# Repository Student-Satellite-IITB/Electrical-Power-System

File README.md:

# ELECTRICAL POWER SYSTEM

This repository contains all software and hardware for the 
Electrical Power subsystem for the IITBSSP CubeSat mission

Current status: 
- EPS PDB and PMB Assembly
- Battery Unit Development Board
- Power Distribution and Regulation Development Board
- MATLAB/Simulink model of EPS in development
- Testing of Solar Input Development Board
- Testing of Control Unit Development Board

Completed:
- EPS PDB Board Design
- EPS PMB Board Design
- Solar Input Development Board
- EPS Control Unit Development Board

Maintained by:
- Ameya Marakarkandy <ameya.marakarkandy@gmail.com>
- Yash Paritkar <paritkary25@gmail.com>

[SSP Website](https://www.aero.iitb.ac.in/satlab/) | 
[Satellite 101 Wiki](https://www.aero.iitb.ac.in/satelliteWiki/index.php/Satellite_101)

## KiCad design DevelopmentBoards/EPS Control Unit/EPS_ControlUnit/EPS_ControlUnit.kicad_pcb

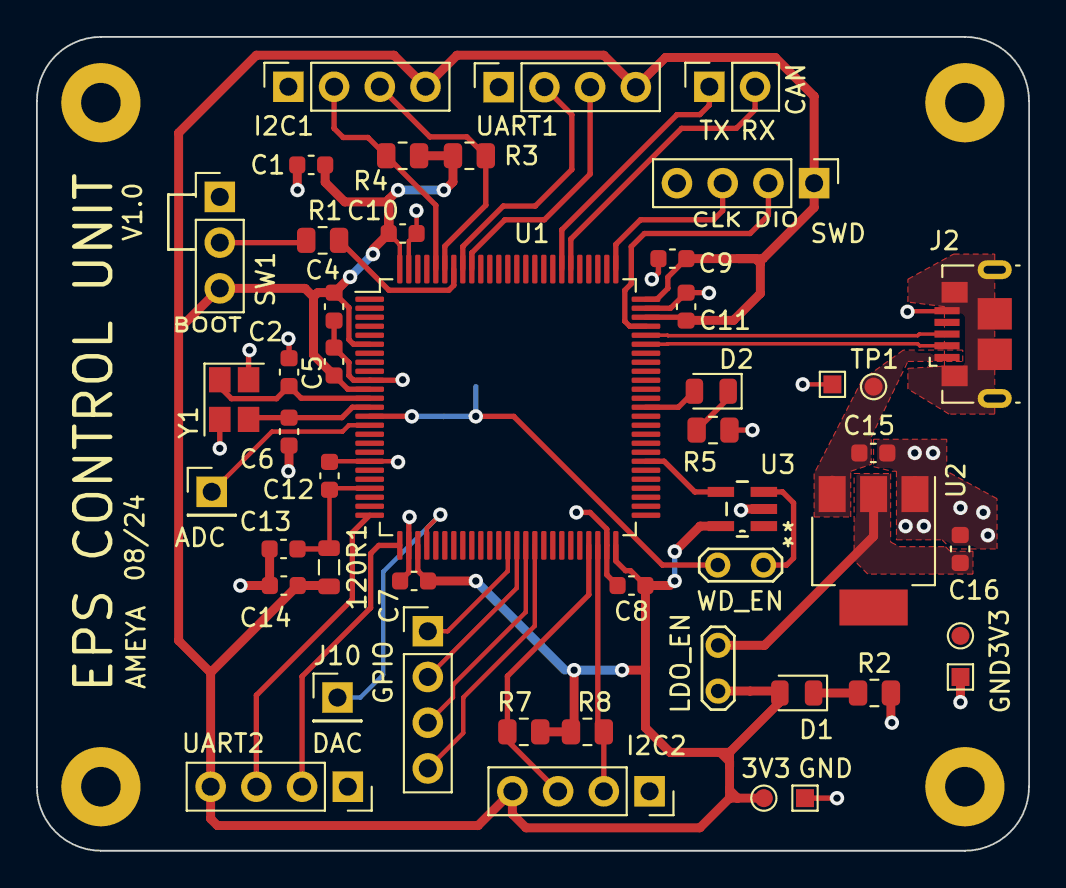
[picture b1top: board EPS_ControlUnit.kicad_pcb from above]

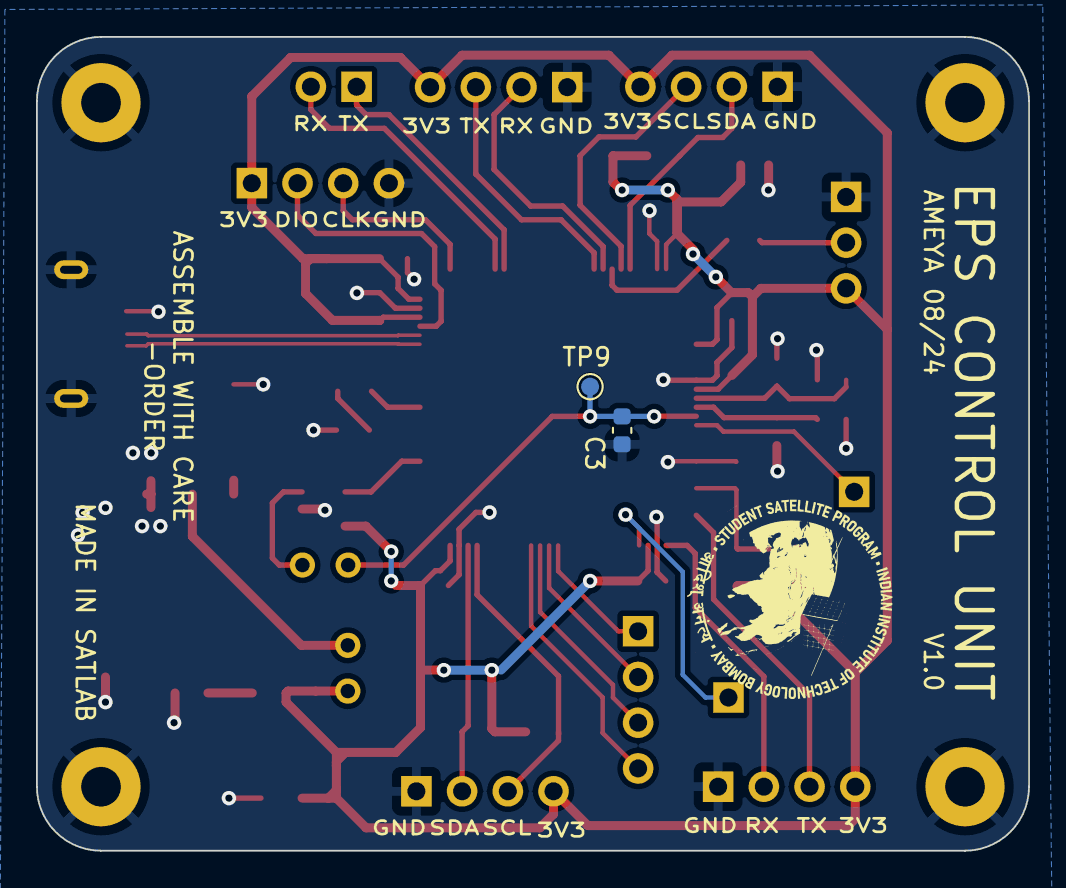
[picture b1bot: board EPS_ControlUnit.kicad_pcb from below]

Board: 2 copper layers, 55.1 x 45.2 mm, 54 parts (2 on the bottom side), 35 nets.

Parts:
3V3, 3V3#2: TestPoint; TestPoint_Pad_D1.0mm
120R1: FerriteBead; L_0805_2012Metric
C1: 10uF; C_0603_1608Metric
C2, C6: 10pF; C_0603_1608Metric
C3, C4, C5, C7, C8, C9, C10, C11: 100nF; C_0603_1608Metric
C12: 10nF; C_0603_1608Metric
C13, C14: 1uF; C_0603_1608Metric
C15, C16: 22uF; C_0603_1608Metric
D1: POWER_LED; LED_0805_2012Metric
D2: EPS_LED; LED_0805_2012Metric
GND: TestPoint; TestPoint_Pad_1.0x1.0mm
GND#2: TestPoint; TestPoint_Pad_1.0x1.0mm
H1, H2, H3, H4: MountingHole_Pad; MountingHole_2.2mm_M2_Pad
J1, J8: Conn_01x04_Pin; PinHeader_1x04_P2.54mm_Vertical
J2: USB_B_Micro; USB_Micro-B_GCT_USB3076-30-A
J3, J4, J5, J6: Conn_01x04_Pin; PinSocket_1x04_P2.54mm_Vertical
J7: Conn_01x02_Pin; PinSocket_1x02_P2.54mm_Vertical
J9, J10: Conn_01x01_Pin; PinHeader_1x01_P2.54mm_Vertical
LDO_EN: Jumper_2_Bridged; TestPoint_2Pads_Pitch2.54mm_Drill0.8mm
R1: 10k; R_0805_2012Metric
R2, R3, R4, R5, R7, R8: 1k5; R_0805_2012Metric
SW1: SW_SPDT; PinHeader_1x03_P2.54mm_Vertical
TP1, TP9: TestPoint; TestPoint_Pad_D1.0mm
TP2: TestPoint; TestPoint_Pad_1.0x1.0mm
U1: STM32L476VET6; LQFP-100_14x14mm_P0.5mm
U2: AMS1117-3.3; SOT-223-3_TabPin2
U3: TPS3824-33QDBVRQ1; tps3824
WD_EN: Jumper_2_Bridged; TestPoint_2Pads_Pitch2.54mm_Drill0.8mm
Y1: 32MHz; Crystal_SMD_Abracon_ABM8AIG-4Pin_3.2x2.5mm

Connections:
3V3_EPS: 3V3.1, 120R1.2, C1.1, C4.1, C5.1, C7.1, C8.1, C9.1, C10.1, C11.1, C14.1, D1.2 (A), J1.1, J3.4, J4.4, J5.4, J6.4, LDO_EN.2 (B), R3.1, R4.1, R7.1, R8.1, SW1.3 (C), U1.6 (VBAT), U1.11 (VDD), U1.28 (VDD), U1.50 (VDD), U1.73 (VDDUSB), U1.75 (VDD), U1.100 (VDD), U3.5 (VDD)
+3.3VA: 120R1.1, C12.1, C13.1, U1.22 (VDDA)
/3V3_LDO: 3V3#2.1, C16.1, LDO_EN.1 (A), U2.2 (VO)
/ADC: J9.1, U1.15 (PC0)
/BOOT0: R1.2, U1.94 (BOOT0)
/CAN_RX: J7.2, U1.81 (PD0)
/CAN_TX: J7.1, U1.82 (PD1)
/DAC: J10.1, U1.29 (PA4)
/EPS_LED: D2.2 (A), U1.63 (PC6)
/GPIO1: J8.1, U1.38 (PE7)
/GPIO2: J8.2, U1.39 (PE8)
/GPIO3: J8.3, U1.40 (PE9)
/GPIO4: J8.4, U1.41 (PE10)
/HSE_IN: C2.1, U1.12 (PH0), Y1.1
/HSE_OUT: C6.1, U1.13 (PH1), Y1.3
/I2C1_SCL: J3.3, R3.2, U1.95 (PB8)
/I2C1_SDA: J3.2, R4.2, U1.96 (PB9)
/I2C2_SCL: J5.3, R7.2, U1.47 (PB10)
/I2C2_SDA: J5.2, R8.2, U1.48 (PB11)
/LED_CATHODE: D1.1 (K), R2.1
/NRST: C3.1, TP9.1, U1.14 (NRST), WD_EN.2 (B)
/SWCLK: J1.3, U1.76 (PA14)
/SWDIO: J1.2, U1.72 (PA13)
/SW_BOOT0: R1.1, SW1.2 (B)
/UART1_RX: J4.2, U1.93 (PB7)
/UART1_TX: J4.3, U1.92 (PB6)
/UART2_RX: J6.2, U1.26 (PA3)
/UART2_TX: J6.3, U1.25 (PA2)
/USB_D+: J2.3 (D+), U1.71 (PA12)
/USB_D-: J2.2 (D-), U1.70 (PA11)
/WDI: U1.57 (PD10), U3.4 (WDI)
/WDI_RESET: U3.3 (RESET), WD_EN.1 (A)
GND: C1.2, C2.2, C3.2, C4.2, C5.2, C6.2, C7.2, C8.2, C9.2, C10.2, C11.2, C12.2, C13.2, C14.2, C15.2, C16.2, GND.1, GND#2.1, H1.1, H2.1, H3.1, H4.1, J1.4, J2.5 (GND), J2.6 (Shield), J3.1, J4.1, J5.1, J6.1, R2.2, R5.2, SW1.1 (A), TP2.1, U1.10 (VSS), U1.19 (VSSA), U1.27 (VSS), U1.49 (VSS), U1.74 (VSS), U1.99 (VSS), U2.1 (GND), U3.2 (GND), Y1.2, Y1.4
unnamed: D2.1 (K), R5.1
VBUS: C15.1, J2.1 (VBUS), TP1.1, U2.3 (VI)

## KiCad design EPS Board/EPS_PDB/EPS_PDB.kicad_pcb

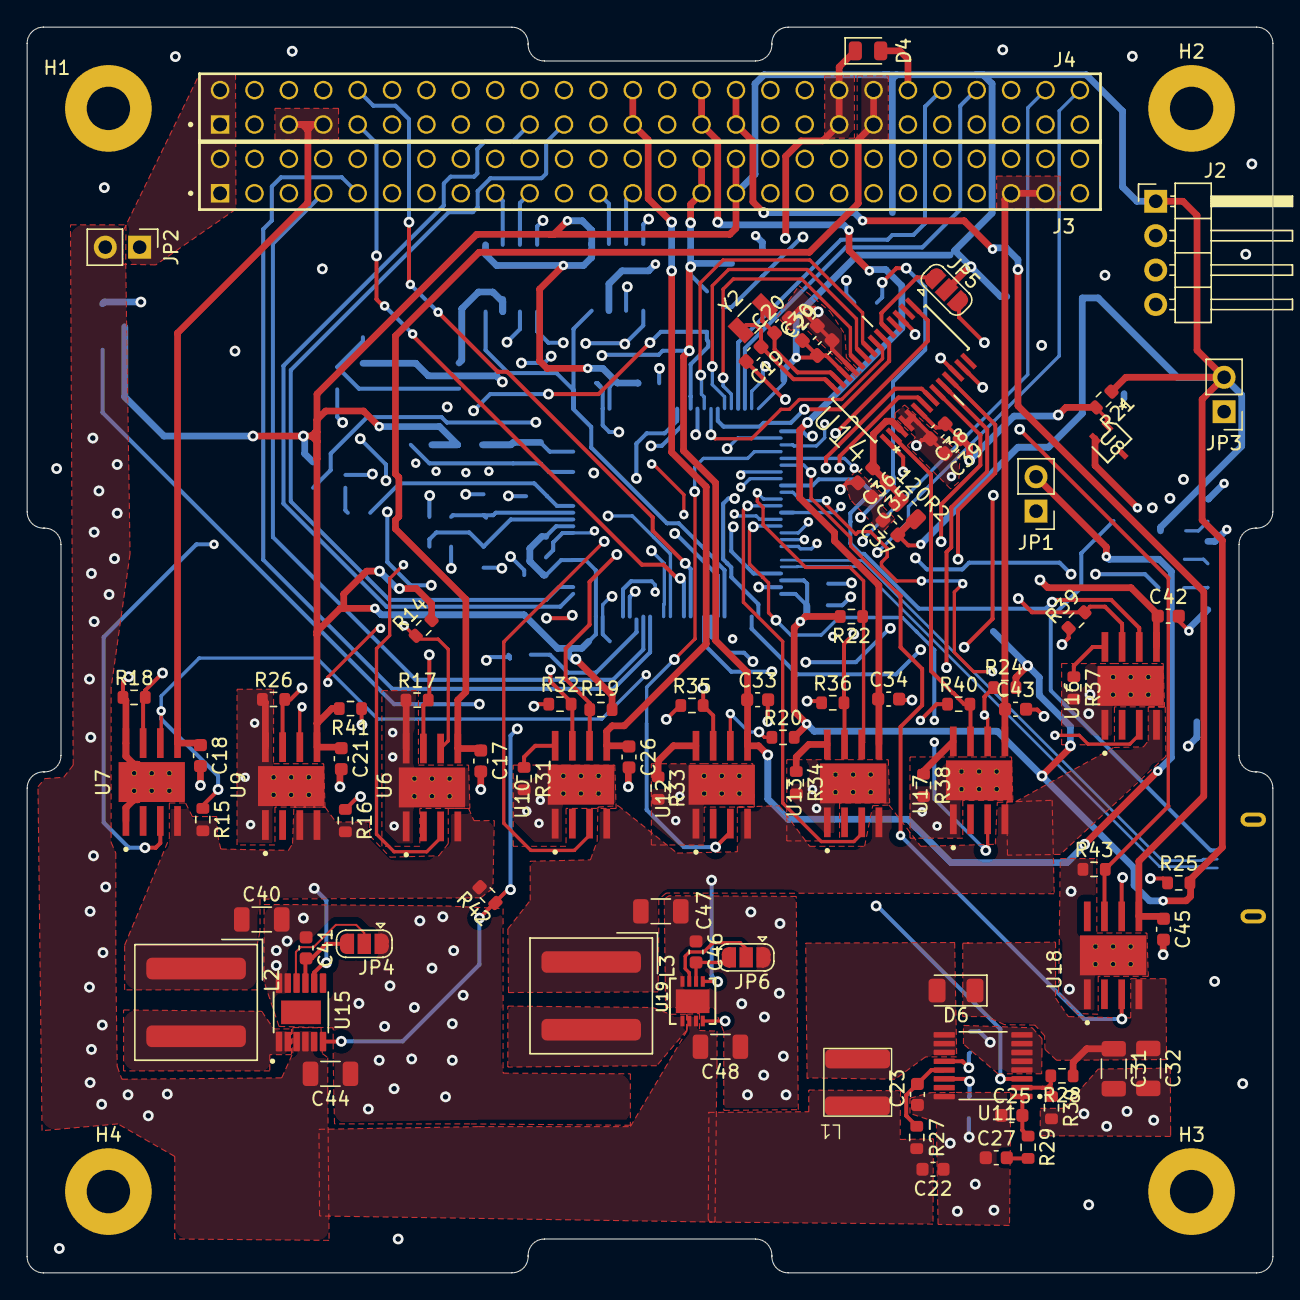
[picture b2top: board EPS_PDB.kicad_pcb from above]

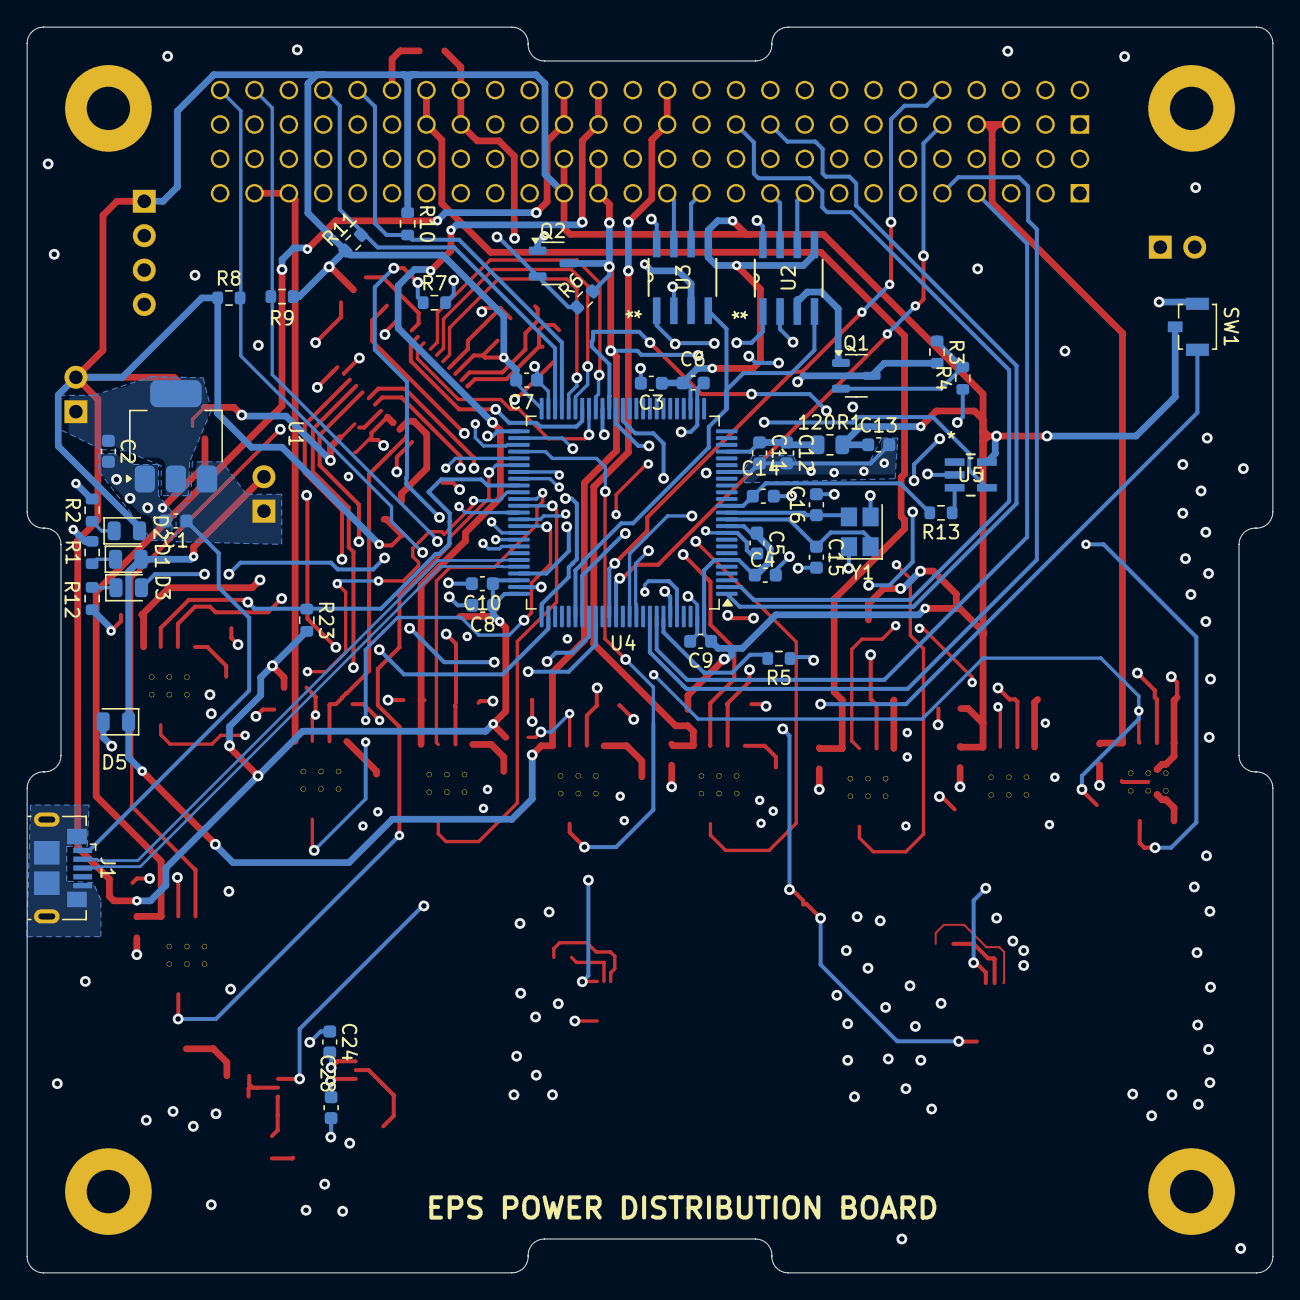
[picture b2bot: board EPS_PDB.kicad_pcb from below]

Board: 4 copper layers, 92.0 x 92.0 mm, 140 parts (47 on the bottom side), 113 nets.

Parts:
120R1, 120R2: FerriteBead; R_0805_2012Metric
C1, C2: 22uF; C_0603_1608Metric
C3, C29, C38: 10uF; C_0603_1608Metric
C4, C5, C6, C7, C8, C9, C10, C14: 100nF; C_0603_1608Metric
C11, C28, C35: 10nF; C_0603_1608Metric
C12, C13, C17, C18, C21, C26, C33, C34, C36, C37, C42, C43, C45: 1uF; C_0603_1608Metric
C15, C16, C19, C20: 10pF; C_0603_1608Metric
C22: 4.7uF; C_0603_1608Metric
C23: 0.47uF; C_0603_1608Metric
C24: 0.1uF; C_0603_1608Metric
C25: 100pF; C_0603_1608Metric
C27: 3300pF; C_0603_1608Metric
C30, C39: C; C_0603_1608Metric
C31, C32: 4.7uF; C_1206_3216Metric
C40, C47: 47uF; C_1206_3216Metric
C41, C46: 2.2uF; C_0603_1608Metric
C44, C48: 10uF; C_1206_3216Metric
D1: EPS_5V_LED; LED_0805_2012Metric
D2: EPS_3V3_LED; LED_0805_2012Metric
D3: EPS_LED; LED_0805_2012Metric
D4, D5: D_Schottky; D_0805_2012Metric
D6: D; D_1206_3216Metric
H1, H2, H3, H4: MountingHole_Pad; MountingHole_3.2mm_M3_Pad
J1: USB_B_Micro; USB_Micro-B_GCT_USB3076-30-A
J2: Conn_01x04_Pin; PinHeader_1x04_P2.54mm_Horizontal
J3, J4: Conn_02x26_Odd_Even; SAMTEC_ESQ-126-39-G-D
JP1, JP3: USB_POW_EN; PinHeader_1x02_P2.54mm_Vertical
JP2: Jumper_2_Bridged; PinHeader_1x02_P2.54mm_Vertical
JP4, JP6: SolderJumper-3_P1.3mm_Open_RoundedPad1.0x1.5mm
JP5: Jumper_3_Bridged12; SolderJumper-3_P1.3mm_Open_RoundedPad1.0x1.5mm
L1: 8.2uH; WE-XHMI-5050
L2, L3: 2.2uH; L_Wuerth_WE-XHMI-8080
Q1, Q2: PMOS; SOT-23-3
R1, R2, R8, R9, R10, R11, R12: 1k5; R_0603_1608Metric
R3, R6: 100k; R_0603_1608Metric
R4, R7: 100; R_0603_1608Metric
R5, R14, R15, R16, R18, R19, R20, R22, R23, R24, R25, R41, R42: 10k; R_0603_1608Metric
R13: 0; R_0603_1608Metric
R17, R26: 2.2k; R_0603_1608Metric
R21, R28: 130k; R_0603_1608Metric
R27: 10; R_0603_1608Metric
R29: 18k; R_0603_1608Metric
R30: 15k; R_0603_1608Metric
R31, R33, R34, R37, R38: 400k; R_0603_1608Metric
R32: 510; R_0603_1608Metric
R35, R39, R43: 560; R_0603_1608Metric
R36, R40: 1.3k; R_0603_1608Metric
SW1: SW_SPDT; SW_SPST_B3U-1100P
U1: AMS1117-3.3; SOT-223-3_TabPin2
U2, U3: SN65HVD256D; D8
U4: STM32L476VET6; LQFP-100_14x14mm_P0.5mm
U5: TPS3824-33QDBVRQ1; tps3824
U6: TPS259621DDAT 3V3_ADCS; IC_TPS259621DDAT
U7: TPS259621DDAT_3V3_ANT; IC_TPS259621DDAT
U8: TS4061BICT-1.25; SOT323-3L_1P35X2P2X0P65_STM
U9: TPS259621DDAT_3V3_EPS; IC_TPS259621DDAT
U10: TPS259621DDAT_5V_PAY; IC_TPS259621DDAT
U11: LM5000-3MTCX; SOP65P640X120-16N
U12: TPS259621DDAT_5V_EPS; IC_TPS259621DDAT
U13: TPS259621DDAT_5V_OBC; IC_TPS259621DDAT
U14: AD7708BRUZ; SOP65P638X110-28N
U15: LTC3624EMSE-3.3PBF; SOP65P490X110-13N
U16: TPS259621DDAT_5V_ADCS; IC_TPS259621DDAT
U17: TPS259621DDAT_5V_COMM; IC_TPS259621DDAT
U18: TPS259621DDAT_12V_ADCS; IC_TPS259621DDAT
U19: LTC3624IDD-25PBF; DFN-8_DD
Y1: 32MHz; Crystal_SMD_Abracon_ABM8AIG-4Pin_3.2x2.5mm
Y2: 32.768kHz; Crystal_SMD_3215-2Pin_3.2x1.5mm

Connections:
3V3_EPS: 120R1.2, 120R2.2, C3.1, C4.1, C5.1, C6.1, C7.1, C8.1, C9.1, C10.1, C13.1, C21.1, C29.1, C30.1, C37.1, D2.2 (A), J2.1, J3.31, J3.32, JP3.2 (B), JP5.2 (C), R8.1, R9.1, R10.1, R11.1, R14.2, R19.2, R20.2, R21.1, R22.2, R23.2, R24.2, R25.2, R41.2, SW1.3 (C), U2.5 (VRXD), U3.5 (VRXD), U4.6 (VBAT), U4.11 (VDD), U4.28 (VDD), U4.50 (VDD), U4.73 (VDDUSB), U4.75 (VDD), U4.100 (VDD), U5.5 (VDD), U9.5 (OUT), U14.26 (DVDD)
5V_EPS: C33.1, D1.2 (A), D5.1 (K), J3.29, J3.30, JP1.2 (B), Q1.3 (S), Q2.3 (S), R3.2, R6.2, U12.5 (OUT)
+3.3VA: 120R1.1, 120R2.1, C11.1, C12.1, C35.1, C36.1, U4.22 (VDDA), U14.3 (AVDD)
/3V3_ADCS: C17.1, J4.39, J4.40, U6.5 (OUT)
/3V3_ANT: C18.1, J4.5, J4.7, U7.5 (OUT)
/3V3_LDO: C2.1, JP3.1 (A), U1.2 (VO)
/5V_ADCS: C42.1, D4.1 (K), J4.37, J4.38, U16.5 (OUT)
/5V_COMM: C43.1, J3.47, J3.49, U17.5 (OUT)
/5V_OBC: C34.1, J4.29, J4.30, U13.5 (OUT)
/5V_PAY: C26.1, J4.25, J4.26, U10.5 (OUT)
/12V_ADCS: C45.1, J4.31, J4.32, U18.5 (OUT)
/ANT_DEPLOY: J4.9, U4.87 (PD6)
/ANT_DEPLOY_STATUS: J4.10, U4.86 (PD5)
/CAN_A_H: J3.19, U2.7 (CANH)
/CAN_A_L: J3.17, U2.6 (CANL)
/CAN_B_H: J3.25, U3.7 (CANH)
/CAN_B_L: J3.23, U3.6 (CANL)
/EN_3V3_ADCS: U4.58 (PD11), U6.3 (EN/UVLO)
/EN_3V3_ANT: U4.67 (PA8), U7.3 (EN/UVLO)
/EN_5V_ADCS: U4.60 (PD13), U16.3 (EN/UVLO)
/EN_5V_COMM: U4.65 (PC8), U17.3 (EN/UVLO)
/EN_5V_EPS: U4.54 (PB15), U12.3 (EN/UVLO)
/EN_5V_OBC: U4.62 (PD15), U13.3 (EN/UVLO)
/EN_5V_PAY: U4.52 (PB13), U10.3 (EN/UVLO)
/EN_12V_ADCS: U4.56 (PD9), U18.3 (EN/UVLO)
/EPS Control Unit/BOOT0: R5.2, U4.94 (BOOT0)
/EPS Control Unit/CAN_RX: U2.4 (RXD), U3.4 (RXD), U4.81 (PD0)
/EPS Control Unit/CAN_SW_A: R4.1, U4.83 (PD2)
/EPS Control Unit/CAN_SW_B: R7.1, U4.84 (PD3)
/EPS Control Unit/CAN_TX: U2.1 (TXD), U3.1 (TXD), U4.82 (PD1)
/EPS Control Unit/EPS_LED: D3.2 (A), U4.63 (PC6)
/EPS Control Unit/HSE_IN: C15.1, U4.12 (PH0), Y1.1
/EPS Control Unit/HSE_OUT: C16.1, U4.13 (PH1), Y1.3
/EPS Control Unit/NRST: C14.1, R13.2, U4.14 (NRST)
/EPS Control Unit/PMOS1_GATE: Q1.2 (G), R3.1, R4.2
/EPS Control Unit/PMOS2_GATE: Q2.2 (G), R6.1, R7.2
/EPS Control Unit/SW_BOOT0: R5.1, SW1.2 (B)
/EPS Control Unit/WDI: U4.38 (PE7), U5.4 (WDI)
/EPS Control Unit/WDI_RESET: R13.1, U5.3 (RESET)
/EPS Power Distribution/1.25VREF: C38.1, C39.1, R21.2, U8.1 (CATHODE), U14.6 (REFIN1(+))
/EPS Power Distribution/3.3V_BUS: C40.1, L2.1, R15.2, R16.2, R42.2, U6.4 (IN), U7.4 (IN), U9.3 (EN/UVLO), U9.4 (IN), U15.8 (FB)
/EPS Power Distribution/5V_BUS: C47.2, L3.1, U10.4 (IN), U12.4 (IN), U13.4 (IN), U16.4 (IN), U17.4 (IN), U19.5 (FB)
/EPS Power Distribution/12V_BUS: C31.1, C32.1, D6.1 (K), R28.1, U18.4 (IN)
/EPS Power Distribution/CLK_IN_ADC: C19.1, U14.28 (XTAL1), Y2.1
/EPS Power Distribution/CLK_OUT_ADC: C20.1, U14.27 (XTAL2), Y2.2
/EPS Power Distribution/FB_12V: R28.2, R30.1, U11.2 (FB)
/EPS Power Distribution/ILM_3V3_ADCS: R17.2, U6.7 (ILM), U14.7 (AIN1)
/EPS Power Distribution/ILM_3V3_ANT: R18.2, U7.7 (ILM), U14.8 (AIN2)
/EPS Power Distribution/ILM_3V3_EPS: R26.2, U9.7 (ILM), U14.9 (AIN3)
/EPS Power Distribution/ILM_5V_ADCS: R39.2, U14.1 (AIN7), U16.7 (ILM)
/EPS Power Distribution/ILM_5V_COMM: R40.2, U14.2 (AIN8), U17.7 (ILM)
/EPS Power Distribution/ILM_5V_EPS: R35.2, U12.7 (ILM), U14.11 (AIN5)
/EPS Power Distribution/ILM_5V_OBC: R36.2, U13.7 (ILM), U14.15 (AIN6)
/EPS Power Distribution/ILM_5V_PAY: R32.2, U10.7 (ILM), U14.10 (AIN4)
/EPS Power Distribution/ILM_12V_ADCS: R43.2, U14.13 (REFIN2(+)/AIN9), U18.7 (ILM)
/EPS Power Distribution/INTVCC_3V3: C41.2, JP4.3 (B), U15.9 (INTVCC)
/EPS Power Distribution/INTVCC_5V: C46.2, JP6.3 (B), U19.6 (INTVCC)
/EPS Power Distribution/MODE_3V3: JP4.2 (C), U15.10 (MODE/SYNC)
/EPS Power Distribution/MODE_5V: JP6.2 (C), U19.7 (MODE/SYNC)
/EPS Power Distribution/SW_3V3: L2.2, U15.1 (SW), U15.2 (SW)
/EPS Power Distribution/SW_5V: L3.2, U19.1 (SW)
/EPS Power Distribution/SW_12V: D6.2 (A), L1.2, U11.9 (SW-1), U11.10 (SW), U11.11 (SW-2)
/EPS Power Distribution/VIN_12V: C23.2, R27.1, U11.13 (VIN)
/FLT_3V3_ADCS: R14.1, U4.57 (PD10), U6.6 (~FLT)
/FLT_3V3_ANT: R15.1, U4.68 (PA9), U7.6 (~FLT)
/FLT_3V3_EPS: R16.1, U4.64 (PC7), U9.6 (~FLT)
/FLT_5V_ADCS: R23.1, U4.59 (PD12), U16.6 (~FLT)
/FLT_5V_COMM: R24.1, U4.66 (PC9), U17.6 (~FLT)
/FLT_5V_EPS: R20.1, U4.53 (PB14), U12.6 (~FLT)
/FLT_5V_OBC: R22.1, U4.61 (PD14), U13.6 (~FLT)
/FLT_5V_PAY: R19.1, U4.51 (PB12), U10.6 (~FLT)
/FLT_12V_ADCS: R25.1, U4.55 (PD8), U18.6 (~FLT)
/HEARTBEAT_ADCS: J4.21, U4.2 (PE3)
/HEARTBEAT_OBC: J4.19, U4.1 (PE2)
/I2C1_SCL: J4.50, R9.2, U4.95 (PB8)
/I2C1_SDA: J4.52, R8.2, U4.96 (PB9)
/I2C2_SCL: J4.44, R10.2, U4.47 (PB10)
/I2C2_SDA: J4.46, R11.2, U4.48 (PB11)
/LED_CATHODE: D2.1 (K), R2.1
/RDY_ADC: U4.42 (PE11), U14.22 (~RDY)
/RESET_ADC: JP5.1 (A), JP5.3 (B), U4.77 (PA15), U14.19 (~RESET)
/SHDN_12V: U4.41 (PE10), U11.3 (SHDN)
/SPI_CS: U4.43 (PE12), U14.21 (~CS)
/SPI_MISO: U4.45 (PE14), U14.23 (DOUT)
/SPI_MOSI: U4.46 (PE15), U14.24 (DIN)
/SPI_SCLK: U4.44 (PE13), U14.20 (SCLK)
/STATUS_3V3: R42.1, U4.40 (PE9), U15.6 (PGOOD)
/STATUS_5V: R41.1, U4.39 (PE8), U19.4 (PGOOD)
/SWCLK: J2.3, U4.76 (PA14)
/SWDIO: J2.2, U4.72 (PA13)
/UART1_CTS: J3.13, U4.90 (PB4)
/UART1_RTS: J3.11, U4.89 (PB3)
/UART1_RX: J3.7, U4.93 (PB7)
/UART1_TX: J3.9, U4.92 (PB6)
/USB_D+: J1.3 (D+), U4.71 (PA12)
/USB_D-: J1.2 (D-), U4.70 (PA11)
/VBUS: C22.2, C44.2, C48.2, JP2.2 (B), L1.1, R27.2, U15.3 (Vin), U15.4 (Vin), U15.5 (RUN), U19.2 (VIN), U19.3 (RUN)
/VBUS0: J3.1, J3.2, J4.1, J4.2, JP2.1 (A)
GND: C1.2, C2.2, C3.2, C4.2, C5.2, C6.2, C7.2, C8.2, C9.2, C10.2, C11.2, C12.2, C13.2, C14.2, C15.2, C16.2, C17.2, C18.2, C19.2, C20.2, C21.2, C22.1, C23.1, C24.1, C25.1, C26.2, C27.1, C28.1, C29.2, C30.2, C31.2, C32.2, C33.2, C34.2, C35.2, C36.2, C37.2, C38.2, C39.2, C40.2, C41.1, C42.2, C43.2, C44.1, C45.2, C46.1, C47.1, C48.1, D4.2 (A), D5.2 (A), H1.1, H2.1, H3.1, H4.1, J1.5 (GND), J1.6 (Shield), J2.4, J3.3, J3.4, J3.15, J3.21, J3.27, J4.3, J4.4, J4.6, J4.8, J4.23, J4.24, J4.27, J4.28, J4.42, J4.48, JP4.1 (A), JP6.1 (A), R1.2, R2.2, R12.2, R17.1, R18.1, R26.1, R30.2, R31.2, R32.1, R33.2, R34.2, R35.1, R36.1, R37.2, R38.2, R39.1, R40.1, R43.1, SW1.1 (A), U1.1 (GND), U2.2 (GND), U2.8 (S), U3.2 (GND), U3.8 (S), U4.10 (VSS), U4.19 (VSSA), U4.27 (VSS), U4.49 (VSS), U4.74 (VSS), U4.99 (VSS), U5.2 (GND), U6.1 (GND), U6.8 (OVCSEL), U6.9 (EXP), U7.1 (GND), U7.8 (OVCSEL), U7.9 (EXP), U8.2 (ANODE), U9.1 (GND), U9.8 (OVCSEL), U9.9 (EXP), U10.1 (GND), U10.9 (EXP), U11.4 (AGND), U11.5 (PGND-1), U11.6 (PGND), U11.7 (PGND-3), U11.8 (PGND-2), U11.16 (TEST), U12.1 (GND), U12.9 (EXP), U13.1 (GND), U13.9 (EXP), U14.4 (AGND), U14.5 (REFIN1(-)), U14.12 (AINCOM), U14.17 (AGND_2), U14.25 (DGND), U15.11 (GND), U15.12 (GND), U16.1 (GND), U16.9 (EXP), U17.1 (GND), U17.9 (EXP), U18.1 (GND), U18.9 (EXP), U19.8 (GND_2), U19.9 (GND), Y1.2, Y1.4
unnamed: C27.2, R29.2
unnamed: D1.1 (K), R1.1
unnamed: D3.1 (K), R12.1
unnamed: Q1.1 (D), U2.3 (VCC)
unnamed: Q2.1 (D), U3.3 (VCC)
unnamed: R31.1, U10.8 (OVCSEL)
unnamed: C24.2, U11.12 (BYP)
unnamed: C25.2, R29.1, U11.1 (COMP)
unnamed: C28.2, U11.14 (SS)
unnamed: R33.1, U12.8 (OVCSEL)
unnamed: R34.1, U13.8 (OVCSEL)
unnamed: R37.1, U16.8 (OVCSEL)
unnamed: R38.1, U17.8 (OVCSEL)
VUSB: C1.1, J1.1 (VBUS), JP1.1 (A), U1.3 (VI)

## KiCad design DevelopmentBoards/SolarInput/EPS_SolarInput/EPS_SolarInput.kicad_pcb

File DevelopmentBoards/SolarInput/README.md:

# EPS Solar Input Unit

Development Board Schematic and PCB Design is complete\
Have sent the PCB for manufacturing\
Yet to order components

Components:
- Molex pico pin connector for input from Solar Panels
- INA232 Current, Volage and Power Measurement with ADC

This document is a work in progress

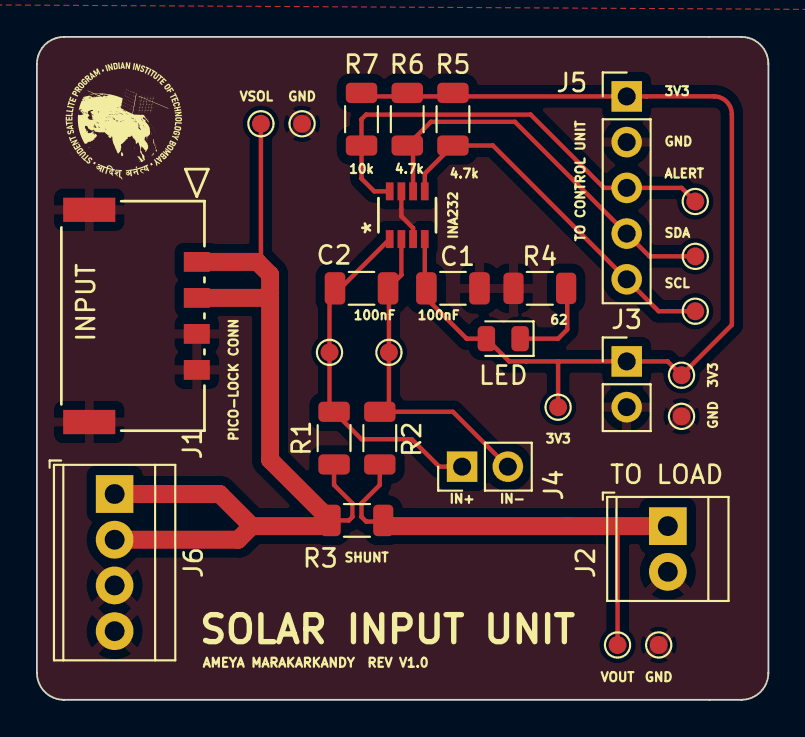
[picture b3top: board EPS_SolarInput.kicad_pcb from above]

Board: 2 copper layers, 40.6 x 36.8 mm, 29 parts (0 on the bottom side), 10 nets.

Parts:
C1: 100nF; C_1206_3216Metric
C2: C2; C_1206_3216Metric
D1: LED; LED_0805_2012Metric
GND: TestPoint; TestPoint_Pad_D1.0mm
INA232: INA232AIDDFR; SOT_32AIDDFR_TEX
J1: 2053380004; CON_2053380004
J2: Screw_Terminal_01x02; TerminalBlock_TE_282834-2_1x02_P2.54mm_Horizontal
J3, J4: Conn_01x02_Socket; PinHeader_1x02_P2.54mm_Vertical
J5: Conn_01x05_Pin; PinHeader_1x05_P2.54mm_Vertical
J6: Screw_Terminal_01x04; TerminalBlock_TE_282834-4_1x04_P2.54mm_Horizontal
R1, R2: <100; R_1206_3216Metric
R3: 40m; R_1206_3216Metric
R4: 62; R_1206_3216Metric
R5, R6: 4.7k; R_1206_3216Metric
R7: 10k; R_1206_3216Metric
TP1, TP2, TP3, TP4, TP5, TP6, TP7, TP8, TP9, TP10: TestPoint; TestPoint_Pad_D1.0mm
VOUT: TestPoint; TestPoint_Pad_D1.0mm

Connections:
+3.3V: C1.2, D1.2 (A), INA232.4 (VS), J3.1, J5.1, R5.1, R6.1, R7.1, TP3.1, TP10.1
/ALERT: INA232.8 (ALERT), J5.3, R7.2, TP8.1
/I2C_SCL: INA232.5 (SCL), J5.5, R5.2, TP6.1
/I2C_SDA: INA232.6 (SDA), J5.4, R6.2, TP7.1
/VSOL: J1.1, J1.2, J6.1, J6.2, R1.1, R3.1, TP1.1
GND: C1.1, GND.1, INA232.3 (GND), INA232.7 (A0), J1.3, J1.4, J1.5, J1.6, J2.2, J3.2, J5.2, J6.3, J6.4, R4.1, TP2.1, TP9.1
unnamed: D1.1 (K), R4.2
unnamed: J2.1, R2.1, R3.2, VOUT.1
unnamed: C2.2, INA232.1 (IN+), J4.1, R1.2, TP4.1
unnamed: C2.1, INA232.2 (IN-), J4.2, R2.2, TP5.1

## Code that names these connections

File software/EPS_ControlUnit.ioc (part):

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Mcu.Name=STM32L476V(C-E-G)Tx
Mcu.Package=LQFP100
Mcu.UserName=STM32L476VETx
PA11.Mode=Device_Only
PA11.Signal=USB_OTG_FS_DM
PA12.Mode=Device_Only
PA12.Signal=USB_OTG_FS_DP
PA13\ (JTMS-SWDIO).Mode=Serial_Wire
PA13\ (JTMS-SWDIO).Signal=SYS_JTMS-SWDIO
PA14\ (JTCK-SWCLK).Mode=Serial_Wire
PA14\ (JTCK-SWCLK).Signal=SYS_JTCK-SWCLK
PA2.Mode=Asynchronous
PA2.Signal=USART2_TX
PA3.Mode=Asynchronous
PA3.Signal=USART2_RX
PA4.GPIOParameters=GPIO_Label
PA4.GPIO_Label=P1_ADC
PA4.Signal=GPIO_Output
PA5.GPIOParameters=GPIO_Label
PA5.GPIO_Label=P2_ADC
PA5.Signal=GPIO_Output
PA6.GPIOParameters=GPIO_Label
PA6.GPIO_Label=RDY_ADC
PA6.Signal=GPIO_Input
PA8.GPIOParameters=GPIO_Label
PA8.GPIO_Label=EN_3V3_ANT
PA8.Signal=GPIO_Output
PA9.GPIOParameters=GPIO_Label
PA9.GPIO_Label=FLT_3V3_ANT
PA9.Signal=GPIO_Input
PB10.Mode=I2C
PB10.Signal=I2C2_SCL
PB11.Mode=I2C
PB11.Signal=I2C2_SDA
PB12.GPIOParameters=GPIO_Label
PB12.GPIO_Label=FLT_5V_PAY
PB12.Signal=GPIO_Input
PB13.GPIOParameters=GPIO_Label
PB13.GPIO_Label=EN_5V_PAY
PB13.Signal=GPIO_Output
PB14.GPIOParameters=GPIO_Label
PB14.GPIO_Label=FLT_5V_EPS
PB14.Signal=GPIO_Input
PB15.GPIOParameters=GPIO_Label
PB15.GPIO_Label=EN_5V_EPS
PB15.Signal=GPIO_Output
PB3\ (JTDO-TRACESWO).Mode=CTS_RTS
PB3\ (JTDO-TRACESWO).Signal=USART1_RTS
PB4\ (NJTRST).Mode=CTS_RTS
PB4\ (NJTRST).Signal=USART1_CTS
PB6.Mode=Asynchronous
PB6.Signal=USART1_TX
PB7.Mode=Asynchronous
PB7.Signal=USART1_RX
PB8.Mode=I2C
PB8.Signal=I2C1_SCL
PB9.Mode=I2C
PB9.Signal=I2C1_SDA
PC0.Signal=ADCx_IN1
PC6.GPIOParameters=GPIO_Label
PC6.GPIO_Label=EPS_LED
PC6.Signal=GPIO_Output
PC7.GPIOParameters=GPIO_Label
PC7.GPIO_Label=FLT_3V3_EPS
PC7.Signal=GPIO_Input
PC8.GPIOParameters=GPIO_Label
PC8.GPIO_Label=EN_5V_COMM
PC8.Signal=GPIO_Output
PC9.GPIOParameters=GPIO_Label
PC9.GPIO_Label=FLT_5V_COMM
PC9.Signal=GPIO_Input
PD0.Mode=CAN_Activate
PD0.Signal=CAN1_RX
PD1.Mode=CAN_Activate
PD1.Signal=CAN1_TX
PD10.GPIOParameters=GPIO_Label
PD10.GPIO_Label=FLT_3V3_ADCS
PD10.Signal=GPIO_Input
PD11.GPIOParameters=GPIO_Label
PD11.GPIO_Label=EN_3V3_ADCS
PD11.Signal=GPIO_Output
PD12.GPIOParameters=GPIO_Label
PD12.GPIO_Label=FLT_5V_ADCS
PD12.Signal=GPIO_Input
PD13.GPIOParameters=GPIO_Label
PD13.GPIO_Label=EN_5V_ADCS
PD13.Signal=GPIO_Output
PD14.GPIOParameters=GPIO_Label
PD14.GPIO_Label=FLT_5V_OBC
PD14.Signal=GPIO_Input
PD15.GPIOParameters=GPIO_Label
PD15.GPIO_Label=EN_5V_OBC
PD15.Signal=GPIO_Output
PD5.GPIOParameters=GPIO_Label
PD5.GPIO_Label=ANT_DEPLOY_STATUS
PD5.Signal=GPIO_Input
PD6.GPIOParameters=GPIO_Label
PD6.GPIO_Label=ANT_DEPLOY
PD6.Signal=GPIO_Output
PD8.GPIOParameters=GPIO_Label
PD8.GPIO_Label=FLT_12V_ADCS
PD8.Signal=GPIO_Input
PD9.GPIOParameters=GPIO_Label
PD9.GPIO_Label=EN_12V_ADCS
PD9.Signal=GPIO_Output
PE10.GPIOParameters=GPIO_Label
PE10.GPIO_Label=SHDN_12V
PE10.Signal=GPIO_Output
PE11.GPIOParameters=GPIO_Label
PE11.GPIO_Label=WDI
PE11.Signal=GPIO_Output
PE12.GPIOParameters=GPIO_Label
PE12.GPIO_Label=SP1_CS
PE12.Signal=GPIO_Output
PE13.Mode=Full_Duplex_Master
PE13.Signal=SPI1_SCK
PE14.Mode=Full_Duplex_Master
PE14.Signal=SPI1_MISO
PE15.Mode=Full_Duplex_Master
PE15.Signal=SPI1_MOSI
PE2.GPIOParameters=GPIO_Label
PE2.GPIO_Label=HBT_OBC
PE2.Signal=GPIO_Input
PE3.GPIOParameters=GPIO_Label
PE3.GPIO_Label=HBT_ADCS
PE3.Signal=GPIO_Input
PE8.GPIOParameters=GPIO_Label
PE8.GPIO_Label=STATUS_5V
PE8.Signal=GPIO_Input
PE9.GPIOParameters=GPIO_Label
PE9.GPIO_Label=STATUS_3V3
PE9.Signal=GPIO_Input
PH0-OSC_IN\ (PH0).Mode=HSE-External-Oscillator
PH0-OSC_IN\ (PH0).Signal=RCC_OSC_IN
PH1-OSC_OUT\ (PH1).Mode=HSE-External-Oscillator
PH1-OSC_OUT\ (PH1).Signal=RCC_OSC_OUT
RCC.HSE_VALUE=32000000
RCC.SYSCLKFreq_VALUE=64000000
RCC.SYSCLKSource=RCC_SYSCLKSOURCE_PLLCLK
board=custom

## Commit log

2023-05-23 P&O Now working
    made some changes in algo +- sign and now P&O is working. Have changed Dinit to 0.7 which is close to the optimal D found by manual tuning
2023-05-24 Step input for irradiation
2024-06-14 Removed cace files and rearranged
2024-06-14 Rearranged files
2024-06-20 Added Design folder with script for energy balance analysis and EPS validation
2024-06-20 Organised filesystem added READMEs
2024-06-20 Started Schematic of Solar Input Development Board
2024-06-21 Completed EPS Solar Input Schematic
2024-06-22 Completed PCB Design for Solar Input Unit Development Board
2024-06-22 Added Board Layout PDF and updated Schematic PDF
2024-06-22 README update
    Added progress in README
2024-06-22 README Updated
2024-06-24 Added KiCAD gitignore file
2024-07-16 Started working on EPS Battery Unit Dev Board
2024-07-18 EPS Final Board
    Started EPS final board schematic
    yet to add dependencies of external libraries to a common folder on GitHub
2024-08-18 Started EPS Control unit design
2024-08-19 EPS Control Unit Dev and Final Schematic designed
2024-08-20 EPS Control Unit Dev Board development
2024-08-29 EPS Control Unit Rough layout done
2024-08-30 EPS Control Unit Dev Board Completed
2024-08-30 README updated
    Updated progress and added image of control unit dev board
2024-09-03 Final changes to EPS Control unit dev board
    Added pinouts for ADC and DAC
    Sent EPS Control unit for manufacturing
    Started designing EPS PDB Board (Control Unit + Power Distribution and Regulation)
2024-09-03 Create delete
2024-09-04 Modified EPS Power Distribution and Regulation Schematic
2024-09-04 Modification of interfaces of EPS Control unit
2024-09-04 Updated Schematic page settings
2024-09-05 MPPT datasheet upload
2024-09-05 DAC datasheet upload
2024-09-05 EPS PDB Board Schematic progress
    Interfaces defined in EPS PDB board Schematic
2024-09-06 EPS PDB Schematic Progress
    Assigned STM32 GPIO pins
2024-09-08 Fixed libraries and updated schematic accordingly
2024-09-08 Added PCB dxf outline
2024-09-08 completed CAN transceiver switching circuit
2024-09-09 Updated to KiCAD 8.0
2024-09-09 test commit
2024-09-09 test commit 2
2024-09-09 test commit 3
2024-09-09 Power Distri & Reg Schematic Complete
2024-09-10 Changed CAN Transceiver IC
    Chose an ic which can operate at 5V Vcc and 3.3V logic
2024-09-10 Added ADC to schematic
2024-09-11 minor changes
2024-09-11 Updated labels from nets
2024-09-11 Bus Pin Definitions added
2024-09-11 Pin definitions of regulaton unit added to root and final changes commments added
2024-09-11 Added Heartbeat GPIOs from ADCS and OBC
2024-09-12 Interfaced Control and PD&R unit
2024-09-14 Reference voltage ic, clock, ADC schematic done
2024-09-15 organise datasheet, add datasheet
    Added datasheet of the battery heater components.
    Renamed all the datasheets to show their short description.
2024-09-17 Added pull up resistors for current limiter
2024-09-17 Created and added the dev board containing all voltage regulators and a current limiter
2024-09-18 simplify datasheet naming
2024-09-19 Revert "Created and added the dev board containing all voltage regulators and a current limiter"
    This reverts commit 38ca713cce1d75051128b490c7247f66081c7b0c.
2024-09-19 texts added in schematics for clarity
2024-09-19 add BMS EVM
2024-09-19 add SAS sims
2024-09-20 Changed PDB dev board location to correct directory
2024-09-21 Footprint assignment on EPS PDB Board
2024-09-21 highlights
2024-09-22 Started EPS PDB PCB Layout
    Modified footprint of PC104 Bus
2024-09-22 PDB PCB Design Progress
    Board outline copy pasted from Antenna Deployment Board
    Added current limiter datasheet
    Routed USB differential pair
2024-09-28 Corrected mistake in USB+LDO circuit on schematic
2024-10-04 EPS PDB Board Layout Progress
    Fixed issue with outline,
    added correct outline
2024-10-05 EPS PDB Layout
    Power Distribution and Regulation unit layout started
2024-10-06 Progresss in EPS PDB Layout
    Voltage Converters and Current limiter section pending
    Might need to increase trace width of power traces on inner layers
2024-10-07 EPS PDB Layout Progress
    Voltage Converter layout pending
2024-10-10 Assigned values to passives of 12V regulator
2024-10-12 Minor changes in EPS PDB Layout
2024-10-16 Add EPS_PMB
2024-10-16 Added decoupling caps to current limiters
2024-10-16 update board and add testing manual
2024-10-16 Assigned all footprints correctly
2024-10-17 minor layout commit
2024-10-17 EPS PDB Board LTC36424 3V3 Layout done
2024-10-17 update silkscreen
2024-10-19 add gerber
2024-10-20 EPS PDB Layout almost complete
    Silkscreen and some minor DRC Issues to be sorted
2024-10-20 EPS PDB Layout Complete
    Have ordered the board
2024-10-20 README updated
    Schematic and Layout PDFs, image added
2024-10-22 Updated EPS PDB BoM
2024-11-05 Update EPS_PMB_Testing_Manual.md
    add errata and grammar check
2024-11-25 Added PMB BOM
2024-12-17 Updated .gitignore
    Modified gitignore file for STM32CubeIDE
2024-12-17 test commit
    to check gitignore file
2024-12-17 Changed folder name
2024-12-17 Deleted software dir
    Will be updating again once directory structure is finalised
2024-12-17 Update .gitignore
    For removing html files in component libraries
2024-12-17 removing gitignored files
2024-12-17 Directory structure update
2024-12-17 Hardware folder added
2024-12-17 linked to EPS Software repo
2024-12-17 Fetched latest version of EPS-Software
2024-12-20 EPS Control Unit Dev Board Software
    Added LED blinking code (EPS_LED) for EPS Control unit development Board.
2025-02-18 Power Generation Simulator Added
2025-03-20 Update ReadMe.md`
2025-03-20 add sch pdf
2025-05-20 major
    Labview HILS, Power Gen Analysis
